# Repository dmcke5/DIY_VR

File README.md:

# CNCDan - DIY VR

A fully 3D printed headset design for VR!

[Project Video Link V1.0](https://youtu.be/pbNyW5GsUQc)

[Project Video Link V2.0](https://youtu.be/7cRuXjuuTN8)

#### Features

- 2880x1440p Resolution
- 120hz Refresh Rate
- Inidividually adjustable IPD
- Easily replaceable lenses
- Compatible with HTC Vive Pro Head Pads
- Adjustable brightness
- SteamVR compatible 3 DOF head tracking or 6DOF using PSMoveServiceEX
- Support for wireless controllers https://github.com/dmcke5/DIY_VR_Controllers

This git has been updated for my Version 2 DIY VR design. All of the original files are still here, they've just been renamed to V1.0 if they are no longer in use (along with the original Readme).

I have included a full model of both versions in .STEP format to aid with assembly!

#### Bill of Materials

1x Display Set - https://www.aliexpress.com/item/32975284107.html

1x GY91 IMU board - https://www.aliexpress.com/item/1005005180963415.html

2x NRF24L01 Wireless Module - https://www.aliexpress.com/item/1005007199963170.html

1x 40mm Ping Pong Balls - https://www.aliexpress.com/item/1005009969506572.html

1x Tactile switch - https://www.aliexpress.com/item/1005006497849129.html

2x 3mm x 145mm Stainless Rod - https://www.aliexpress.com/item/1005009347568195.html

6x 3x6(OD) 4mm(L) Brass Bushings - https://www.aliexpress.com/item/1005008668212038.html

1x Arduino Pro Micro USB-C Version - https://www.aliexpress.com/item/32846843498.html

1x Pair 34mm Diameter 45mm Focal Length Lenses - https://www.aliexpress.com/item/1005004324103470.html

1x 1M 25mm Nylon Strapping - https://www.aliexpress.com/item/1005008515249414.html

1x HTC Vive Pro Face Pad - https://www.aliexpress.com/item/1005001324834346.html

#### Hardware

16x M3x5x5 Threaded Inserts

4x M3x12 SHCS

10x M3x8 SHCS

4x M3x12 Standoffs

### Instructions

#### Printing

First, you'll need one of every part printed, except for these items that require multiples:

3x DIY VR Buckle 

2x DIY VR Lens Retainer

2x DIY VR Thumbscrew Head

The files with V1.0 names can be ignored, unless you are specifically making the old version in which case, you can print them and disregard any V2.0 files. Refer the to V1.0 readme for specific Instructions.

There are print recomendations for most of the important parts in the first video.
The V2.0 front cover is much easier to print than V1.0 and can be printed front down with minimal supports.

#### Electronics

Only three SMD parts are required to assemble the PCB, 1x MCP1792-3302xCB and two 470nF 0603 Capacitors. The two NRF modules can be soldered in as usual, but when you solder in the IMU module ensure you remove the black plastic spacer from the pins to ensure the module is sitting flat against the PCB. The Arduino needs to be installed WITH the black plastic spacers, otherwise its USB port won't align with the opening.

Once the head tracker board is assembled, there are three sets of pads you will need to connect. The two pads labelled "Calibrate" are to be wired to the tactile switch on the side of the headset. The three pads labelled VCC, GND and DO are to be connected to an addressable RGB LED that is used for the pingpong ball.
The final two pads labelled VCC and GND are to supply power to your display driver and should be connected accordingly.

#### Head Tracking Software/Firmware

Revision 2.0 of the head tracker relies on the HadesVR driver. I have included a slightly modified version of their firmware here, which you will need to use as it adds support for the addressable RGB led used for the tracking bulb.

Refer to the HadesVR github page for upload and config instructions: 
https://github.com/HadesVR/Basic-HMD-PCB?tab=readme-ov-file#uploading-the-firmware-and-calibrating-the-sensors

If you're using the 6DOF tracking, you will also need to go through the PSMoveServiceEX Setup process. Their documentation is here: https://github.com/Timocop/PSMoveServiceEx/wiki

#### Physical Build

Refer to both of the project videos for build steps and I will add anything here in future if anyone requests extra information!

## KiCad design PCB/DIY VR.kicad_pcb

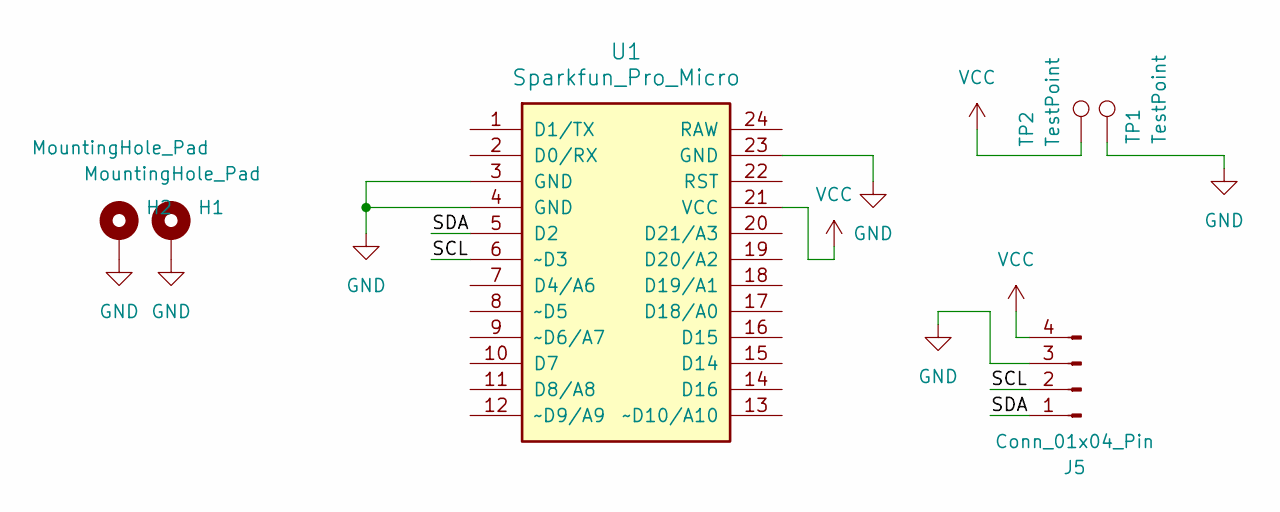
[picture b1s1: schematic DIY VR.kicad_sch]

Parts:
H1, H2: MountingHole_Pad; MountingHole_3.2mm_M3_DIN965_Pad
J5: Conn_01x04_Pin; PinHeader_1x04_P2.54mm_Vertical
TP1, TP2: TestPoint; Pin_D1.3mm_L11.0mm
U1: Sparkfun_Pro_Micro

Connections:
/SCL: J5.2, U1.6 (~D3)
/SDA: J5.1, U1.5 (D2)
GND: H1.1, H2.1, J5.3, TP1.1, U1.3 (GND), U1.4 (GND), U1.23 (GND)
VCC: J5.4, TP2.1, U1.21 (VCC)

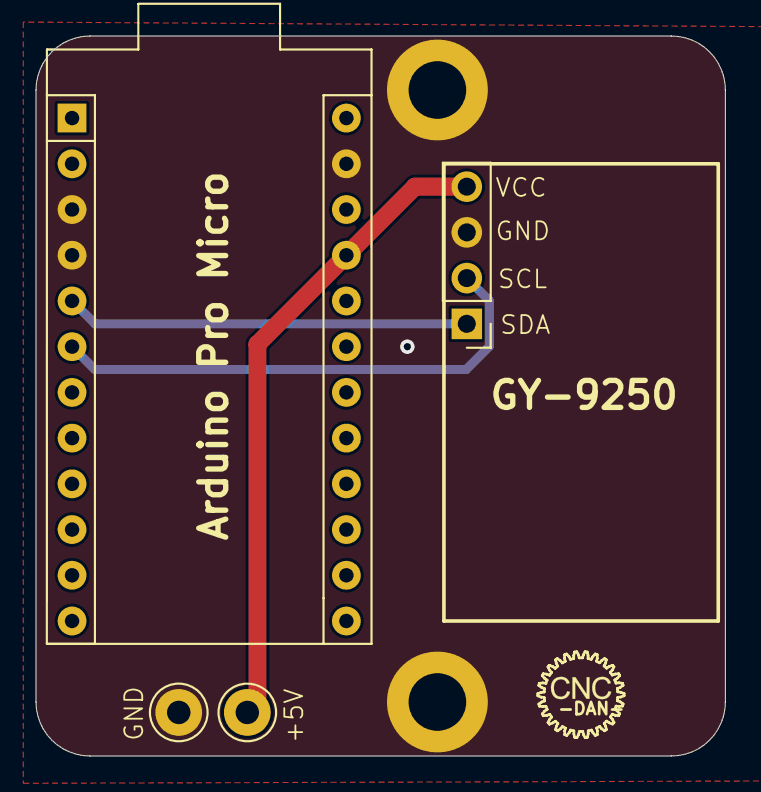
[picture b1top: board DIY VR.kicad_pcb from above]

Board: 2 copper layers, 38.3 x 40.0 mm, 6 parts (0 on the bottom side), 4 nets.

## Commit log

2025-09-19 Add license and readme
2025-09-19 Added files for PCB
2025-09-19 Added STL's
2025-09-22 Added full assembly model and STL's
2025-09-22 Replaced Title Image
2025-12-01 Updated to V2.0!
